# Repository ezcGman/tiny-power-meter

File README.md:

# Tiny 3-phase power meter
A very tiny ESP8266 based PCB to monitor your apartments / homes power consumption using CT clamps and report the reading to Home Assistant using ESPHome!

## Credits
As for all my PCBs: Huge thanks to Quindor from QuinLED.info and also the folks from #pcb-design-talk on his Discord server! Would not have been able to do anything without these people!!

## KiCad dependencies
It might happen that KiCad is missing my custom footprints. You can find and download them here and then add them to KiCad: https://github.com/ezcGman/andys-footprints

## Key features
TBD

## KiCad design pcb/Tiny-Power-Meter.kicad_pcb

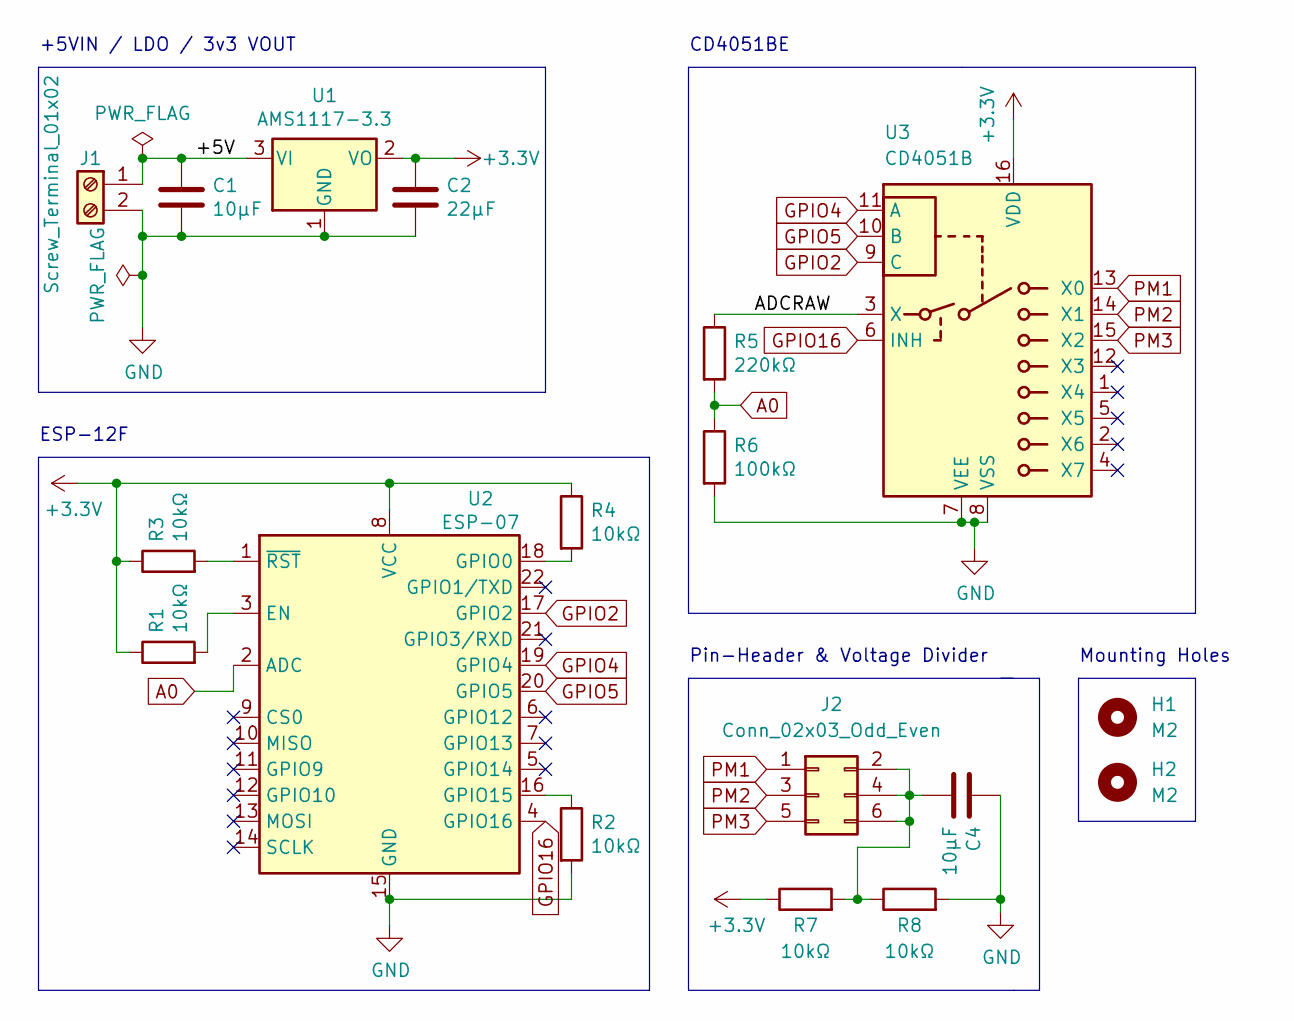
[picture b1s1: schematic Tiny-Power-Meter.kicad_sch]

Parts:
C1, C4: 10µF; C_0805_2012Metric
C2: 22µF; C_0805_2012Metric
H1, H2: M2; MountingHole_2.2mm_M2_Pad_Via
J1: Screw_Terminal_01x02; TerminalBlock_Phoenix_MPT-0,5-2-2.54_1x02_P2.54mm_Horizonta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
J2: Conn_02x03_Odd_Even; PinHeader_2x03_P2.54mm_Horizontal
R1, R2, R3, R4, R7, R8: 10kΩ; R_0805_2012Metric
R5: 220kΩ; R_0805_2012Metric
R6: 100kΩ; R_0805_2012Metric
U1: AMS1117-3.3; SOT-223-3_TabPin2
U2: ESP-07; ESP-12-Socket-Cutout
U3: CD4051B; DIP-16_W7.62mm

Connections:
+3V3: C2.1, R1.1, R3.1, R4.1, R7.1, U1.2 (VO), U2.8 (VCC), U3.16 (VDD)
/+5V: C1.1, J1.1, U1.3 (VI)
/ADCRAW: R5.1, U3.3 (X)
A0: R5.2, R6.1, U2.2 (ADC)
GND: C1.2, C2.2, C4.1, J1.2, R2.2, R6.2, R8.2, U1.1 (GND), U2.15 (GND), U3.7 (VEE), U3.8 (VSS)
GPIO2: U2.17 (GPIO2), U3.9 (C)
GPIO4: U2.19 (GPIO4), U3.11 (A)
GPIO5: U2.20 (GPIO5), U3.10 (B)
GPIO16: U2.4 (GPIO16), U3.6 (INH)
unnamed: C4.2, J2.2, J2.4, J2.6, R7.2, R8.1
unnamed: R1.2, U2.3 (EN)
unnamed: R2.1, U2.16 (GPIO15)
unnamed: R3.2, U2.1 (~RST)
unnamed: R4.2, U2.18 (GPIO0)
PM1: J2.1, U3.13 (X0)
PM2: J2.3, U3.14 (X1)
PM3: J2.5, U3.15 (X2)

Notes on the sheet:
CD4051BE
Mounting Holes
+5VIN / LDO / 3v3 VOUT
Pin-Header & Voltage Divider
ESP-12F

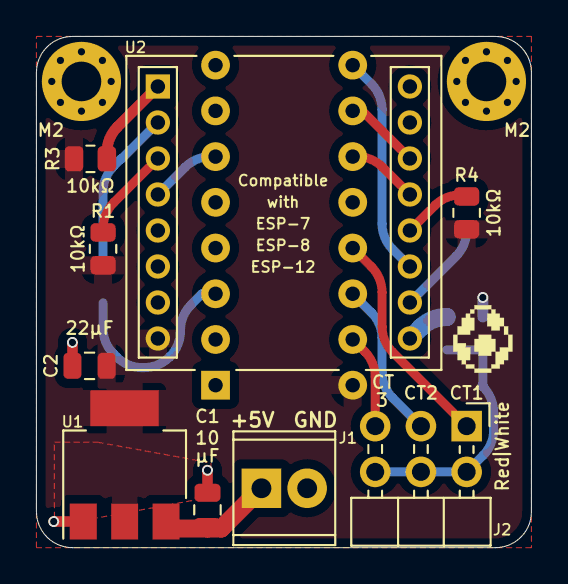
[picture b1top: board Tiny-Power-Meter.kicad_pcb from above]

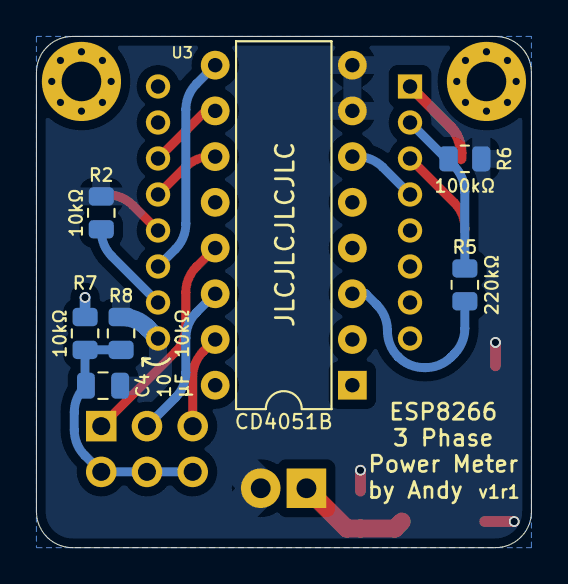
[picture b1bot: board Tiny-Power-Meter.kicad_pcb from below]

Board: 2 copper layers, 27.5 x 28.4 mm, 18 parts (7 on the bottom side), 17 nets.

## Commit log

2022-09-28 First commit of v1r1
2022-09-28 Added missing pictures
